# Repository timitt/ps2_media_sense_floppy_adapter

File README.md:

# PS/2 Media Sense Floppy Adapter

This adapter allows to use standard floppy drive or Gotek drive (with FlashFloppy firmware) on IBM PS/2 computers
that have Media Sense drives. Using this adapter you can boot from Starter Disk and configure your computer.
Also error codes regarding floppy drive are history.

Adapter allows to be configured to 1.44 MB and 2.88 MB FDD drive with Media Sense.
This is not tested with real 2.88 MB though as I do not own one.

It should be possible to use multiple drives with this adapter.

1.2 MB FDD mode is currently untested. My guess is that 1.2 MB drive can't be used as A drive.

## Jumpers

If neither 1.2 floppy and 2.88 floppy jumpers are shorted then drive is 1.44 MB floppy.

Shorting JP1 pins 2 and 3 (bottom ones) you send density info from computer which is the normal way floppy drives work.
However later 1.44 MB and likely 2.88 MB drives do not use this signal.

Gotek can be configured to send density info from drive and therefore actually send Media Sense info.
This only works when drive is 1.44 MB drive. In this case you short JP1 pins 1 and 2 (top ones) and JP2.

Typically JP1 and JP2 can be without jumpers and all works well.

## Resistor Network

Resistor network is not needed with Gotek drive as it has 1kOhm pull up resistors already.

Only 6 pin resistor network is needed. Rest are unused.

Possible options for resistance are 1kOhm, 4.7kOhm or 10kOhm. Tests are done with 4.7kOhm resistor network.

## Building

Everything is through hole stuff and easy to solder.

GAL16V8D chip can be programmed with TL866 programmer using JED file in gal folder.

It is highly recommended to use quite short cable between adapter and floppy drive.
Long cables seem to cause random errors.

## Tested Computers

* PS/2 Model 40 SX

(Feel free to report other working machines)

## License

(c) Timi Tuohenmaa, 2023

This work is licensed under CC BY 4.0. To view a copy of this license, visit http://creativecommons.org/licenses/by/4.0/

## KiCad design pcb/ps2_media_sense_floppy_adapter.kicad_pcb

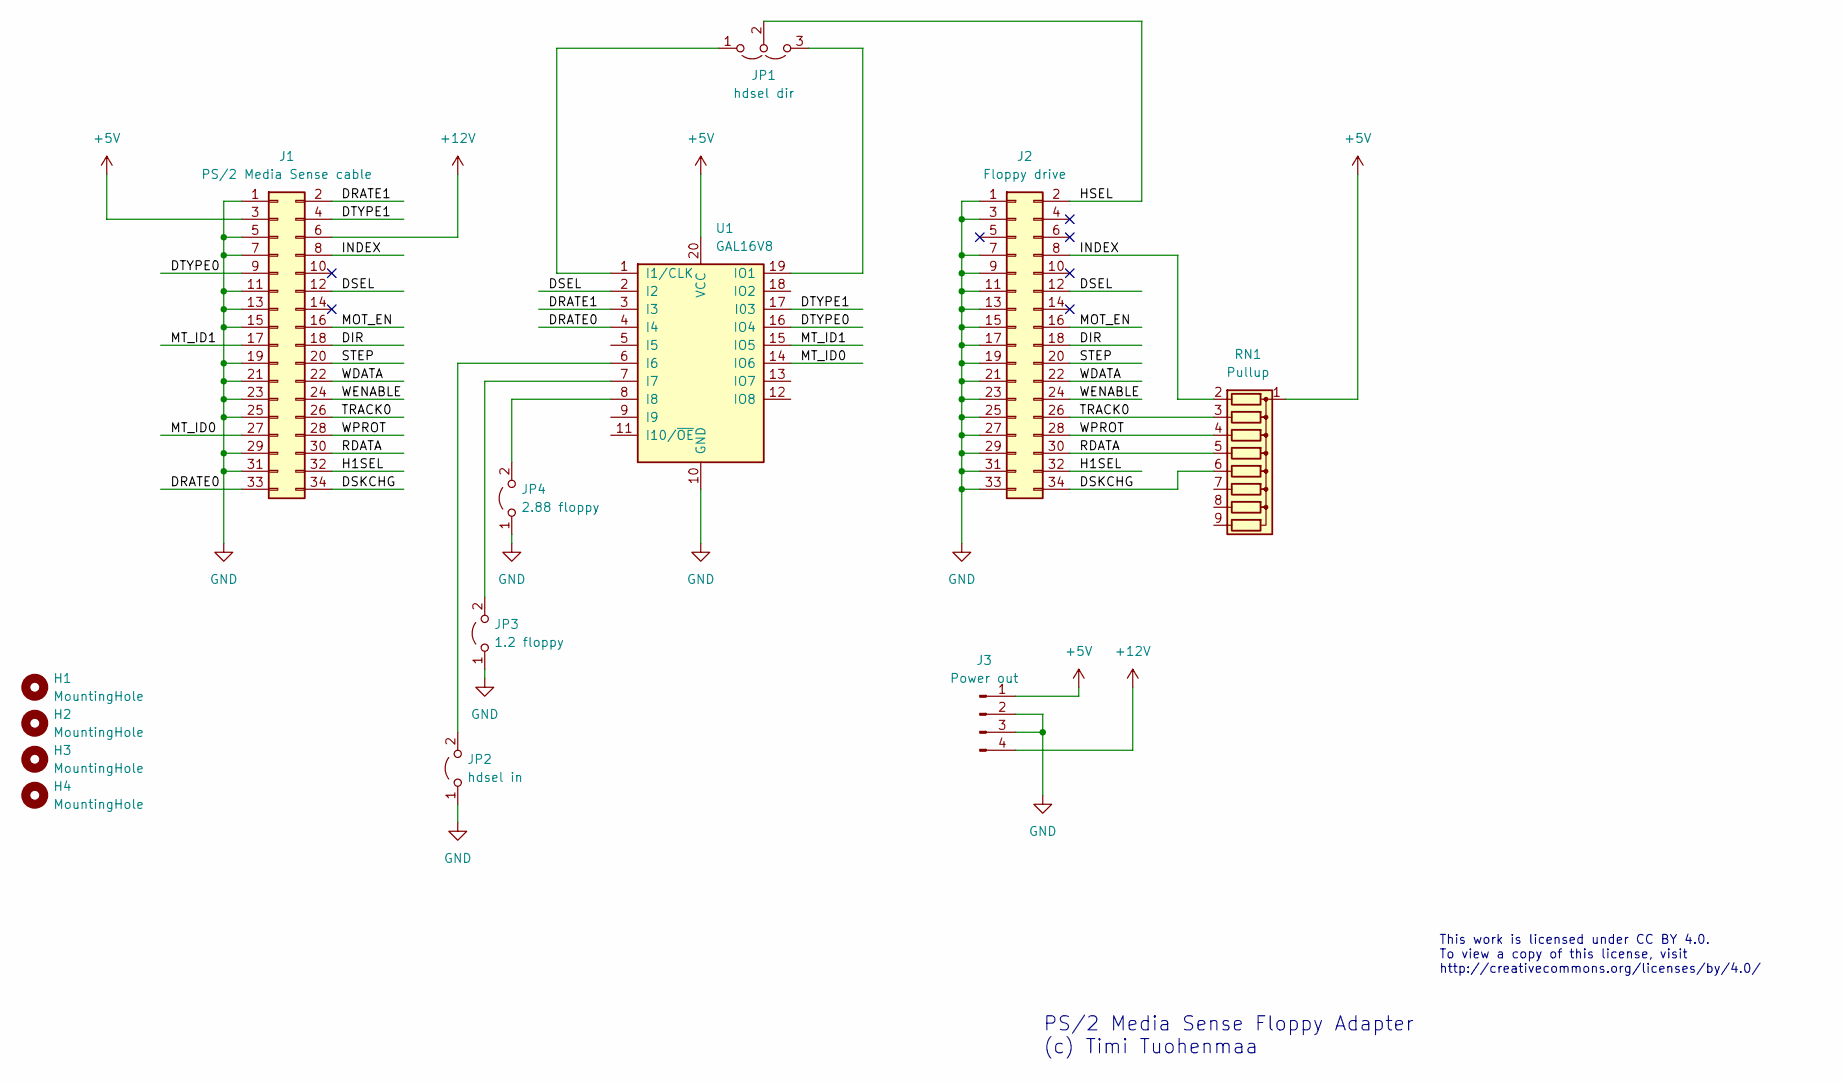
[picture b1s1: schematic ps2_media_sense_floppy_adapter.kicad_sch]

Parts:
H1, H2, H3, H4: MountingHole; MountingHole_3.2mm_M3
J1: PS/2 Media Sense cable; IDC-Header_2x17_P2.54mm_Vertical
J2: Floppy drive; IDC-Header_2x17_P2.54mm_Vertical
J3: Power out; PinHeader_1x04_P2.54mm_Vertical
JP1: hdsel dir; PinHeader_1x03_P2.54mm_Vertical
JP2: hdsel in; PinHeader_1x02_P2.54mm_Vertical
JP3: 1.2 floppy; PinHeader_1x02_P2.54mm_Vertical
JP4: 2.88 floppy; PinHeader_1x02_P2.54mm_Vertical
RN1: Pullup; R_Array_SIP9
U1: GAL16V8; DIP-20_W7.62mm_Socket

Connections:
+5V: J1.3, J3.1, RN1.1 (common), U1.20 (VCC)
+12V: J1.6, J3.4
/DIR: J1.18, J2.18
/DRATE0: J1.33, U1.4 (I4)
/DRATE1: J1.2, U1.3 (I3)
/DSEL: J1.12, J2.12, U1.2 (I2)
/DSKCHG: J1.34, J2.34, RN1.6 (R5)
/DTYPE0: J1.9, U1.16 (IO4)
/DTYPE1: J1.4, U1.17 (I03)
/H1SEL: J1.32, J2.32
/HSEL: J2.2, JP1.2 (C)
/INDEX: J1.8, J2.8, RN1.2 (R1)
/MOT_EN: J1.16, J2.16
/MT_ID0: J1.27, U1.14 (IO6)
/MT_ID1: J1.17, U1.15 (IO5)
/RDATA: J1.30, J2.30, RN1.5 (R4)
/STEP: J1.20, J2.20
/TRACK0: J1.26, J2.26, RN1.3 (R2)
/WDATA: J1.22, J2.22
/WENABLE: J1.24, J2.24
/WPROT: J1.28, J2.28, RN1.4 (R3)
GND: J1.1, J1.5, J1.7, J1.11, J1.13, J1.15, J1.19, J1.21, J1.23, J1.25, J1.29, J1.31, J2.1, J2.3, J2.7, J2.9, J2.11, J2.13, J2.15, J2.17, J2.19, J2.21, J2.23, J2.25, J2.27, J2.29, J2.31, J2.33, J3.2, J3.3, JP2.1 (A), JP3.1 (A), JP4.1 (A), U1.10 (GND)
unnamed: JP1.1 (A), U1.1 (I1/CLK)
unnamed: JP1.3 (B), U1.19 (IO1)
unnamed: JP2.2 (B), U1.6 (I6)
unnamed: JP3.2 (B), U1.7 (I7)
unnamed: JP4.2 (B), U1.8 (I8)

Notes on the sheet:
This work is licensed under CC BY 4.0. To view a copy of this license, visit http://creativecommons.org/licenses/by/4.0/
PS/2 Media Sense Floppy Adapter (c) Timi Tuohenmaa

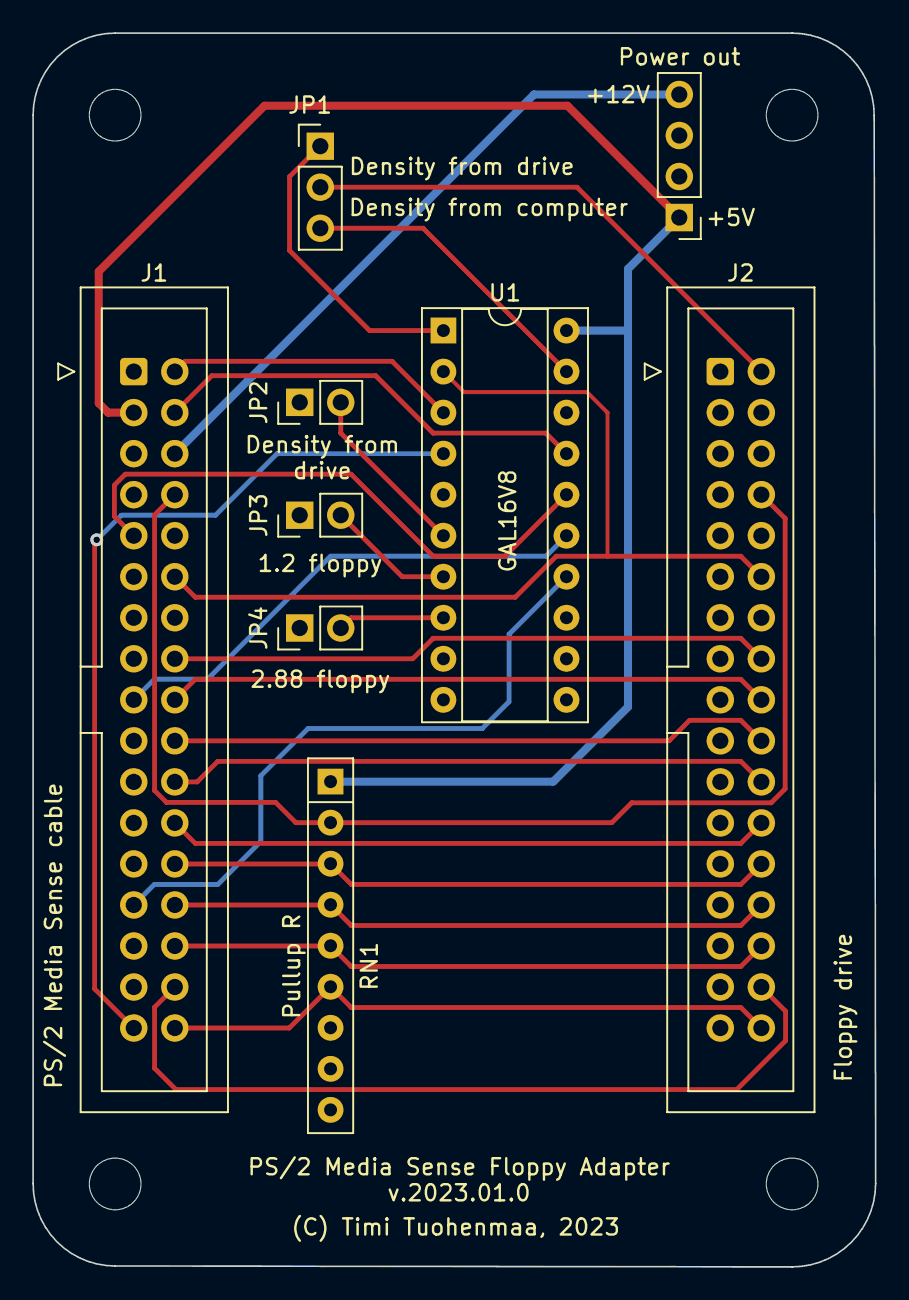
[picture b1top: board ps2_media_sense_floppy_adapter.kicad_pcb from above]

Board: 2 copper layers, 52.2 x 76.4 mm, 13 parts (0 on the bottom side), 27 nets.

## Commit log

2023-03-18 Added image link
2023-03-18 Fixed some typos and added more info.
